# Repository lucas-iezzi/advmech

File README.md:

# Advanced Mechatronics
Welcome to my repo for Advanced Mechatronics (ME 433)

See the [demo](https://youtube.com/shorts/6-6EqAZjXH0) of my final robot which uses a gyro to drive towards a specific heading.
This video shows it calibrating then adjusting the heading from -1 to 1 and back, making a figure 8.
The drive motors are controlled using a PIC32 with and IMU for feedback.
The Pico uses a camera to detect a line on the ground and eventually it will send a heading to the drive board over UART based on where the line is.

See Final/Pictures for more pictures

__Chips Used__
* PIC32MX170F256B (PIC32)
* AP7381 (3.3V Regualtor)
* MCP4912 (10-bit DAC over SPI)
* MCP23008 (8-bit IO Expander over I2C)
* MPU6050 (IMU over I2C)
* SSD1306 (I2C OLED Display)
* WS2812B (LED NeoPixels)
* ST7735 (LCD Screen I2C)
* OV7670 (I2C Camera)
* RP2040 (RPi Pico W)

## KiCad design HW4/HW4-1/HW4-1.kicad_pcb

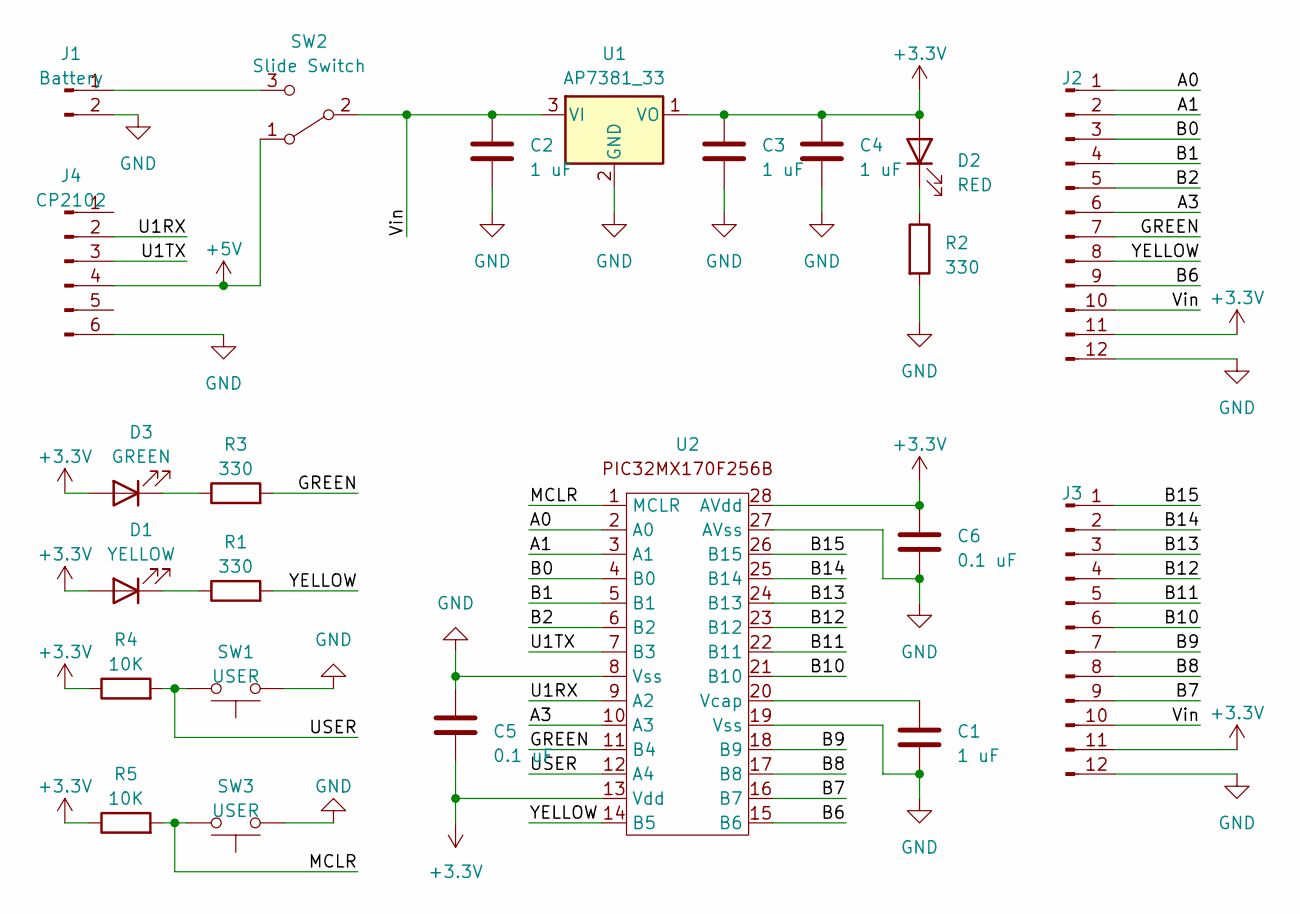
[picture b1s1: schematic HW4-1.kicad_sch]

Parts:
C1, C2, C3, C4: 1 uF; C_Disc_D4.3mm_W1.9mm_P5.00mm
C5, C6: 0.1 uF; C_Disc_D3.0mm_W2.0mm_P2.50mm
D1: YELLOW; LED_D3.0mm
D2: RED; LED_D3.0mm
D3: GREEN; LED_D3.0mm
J1: Battery; PinSocket_1x02_P2.54mm_Vertical
J2, J3: PinSocket_1x12_P2.54mm_Vertical
J4: CP2102; PinSocket_1x06_P2.54mm_Vertical
R1, R2, R3: 330; R_Axial_DIN0207_L6.3mm_D2.5mm_P7.62mm_Horizontal
R4, R5: 10K; R_Axial_DIN0207_L6.3mm_D2.5mm_P7.62mm_Horizontal
SW1, SW3: USER; pushbtn
SW2: Slide Switch; slidesw
U1: AP7381_33; TO-92L_Inline_Wide
U2: DIP-28_W7.62mm_Socket

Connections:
+3.3V: C3.1, C4.1, C5.2, C6.1, D1.2 (A), D2.2 (A), D3.2 (A), J2.11, J3.11, R4.1, R5.1, U1.1 (VO), U2.13 (Vdd), U2.28 (AVdd)
+5V: J4.4, SW2.1 (A)
/A0: J2.1, U2.2 (A0)
/A1: J2.2, U2.3 (A1)
/A3: J2.6, U2.10 (A3)
/B0: J2.3, U2.4 (B0)
/B1: J2.4, U2.5 (B1)
/B2: J2.5, U2.6 (B2)
/B6: J2.9, U2.15 (B6)
/B7: J3.9, U2.16 (B7)
/B8: J3.8, U2.17 (B8)
/B9: J3.7, U2.18 (B9)
/B10: J3.6, U2.21 (B10)
/B11: J3.5, U2.22 (B11)
/B12: J3.4, U2.23 (B12)
/B13: J3.3, U2.24 (B13)
/B14: J3.2, U2.25 (B14)
/B15: J3.1, U2.26 (B15)
/GREEN: J2.7, R3.2, U2.11 (B4)
/MCLR: R5.2, SW3.2, U2.1 (MCLR)
/U1RX: J4.2, U2.9 (A2)
/U1TX: J4.3, U2.7 (B3)
/USER: R4.2, SW1.2, U2.12 (A4)
/Vin: C2.1, J2.10, J3.10, SW2.2 (B), U1.3 (VI)
/YELLOW: J2.8, R1.2, U2.14 (B5)
GND: C1.2, C2.2, C3.2, C4.2, C5.1, C6.2, J1.2, J2.12, J3.12, J4.6, R2.2, SW1.1, SW3.1, U1.2 (GND), U2.8 (Vss), U2.19 (Vss), U2.27 (AVss)
unnamed: D1.1 (K), R1.1
unnamed: D2.1 (K), R2.1
unnamed: D3.1 (K), R3.1
unnamed: J1.1, SW2.3 (C)
unnamed: C1.1, U2.20 (Vcap)

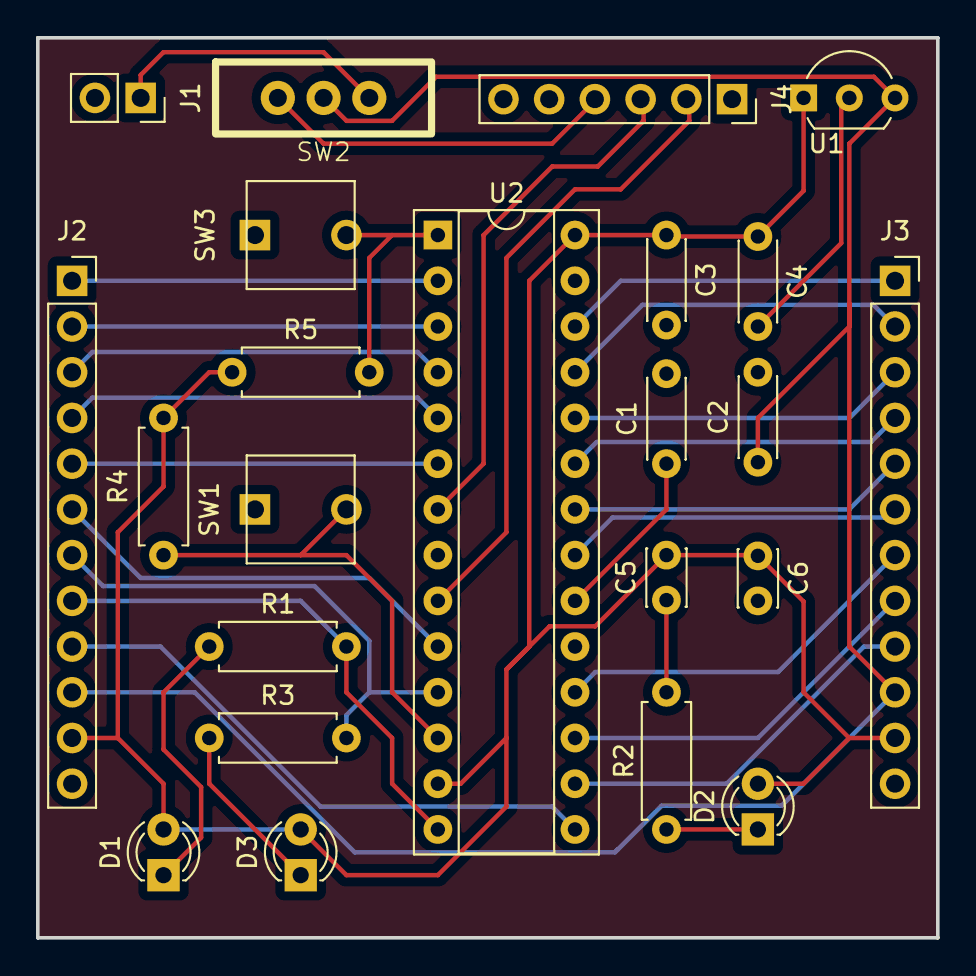
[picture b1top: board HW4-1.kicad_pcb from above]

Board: 2 copper layers, 50.0 x 50.0 mm, 23 parts (0 on the bottom side), 31 nets.

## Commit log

2023-03-30 Create 19f64a4f397fe4896f0b29c3e36832059974aa86
2023-03-30 Create 4738b1ecbe1a81e18a72118ba3d815d97a4c90be
2023-03-30 Create 61c10a8bcbc8a288164369ba4ec9868827f0f907
2023-03-30 Create d6dc60801185544989ef0c9895d1336ce64b5931
2023-03-30 Create da39a3ee5e6b4b0d3255bfef95601890afd80709
2023-03-30 files
2023-03-30 utility
2023-03-31 day 1
2023-04-06 deliverables
2023-04-06 HW3 done
2023-04-19 HW5 Done
2023-04-21 HW6 Done
2023-04-25 HW7 done
2023-04-26 HW8 done
2023-05-03 HW10 done
2023-05-11 HW 9 Done
2023-05-15 HW11 Done
2023-05-23 HW13 Done
2023-06-03 Final Dump
2023-06-03 HW15
2023-06-03 Finished
